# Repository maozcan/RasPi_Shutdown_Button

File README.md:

# Raspberry Pi Shutdown/Restart Button

## Hardware setup
Raspberry Pi GPIO pins are being used to send 'shutdown' command to turn off the Pi and to restart the device from off status.

Physical GPIO pin#7 turns off the system when you press switch#1 for 3+ seconds. The LED that is connected to pin#11 starts to blink and the shutdown routine is triggered. (LED is on when the system is operational.)

While the system is turned off, if the user presses the switch#2 which is connected to pin#5, RasPi gets a reboot signal and the system turns on.

EagleCad [schematic](/PiShutdownButton.sch) and [board](/PiShutdownButton.brd) layouts are available for download:

The board is then processed using CNC isolation routing; gcode created using php-gcode ULP and then the board is prepared on CNC machine. The pin headers have been soldered parallel to the board to help easier connection to RasPi board.

## Software setup

Python is used to handle the GPIO operations.

Install Python3 if it's not already installed. Also reinstall rpi.gpio package to ensure it is up to date.

```
> sudo apt-get install python3 rpi.gpio
```

Add the python script to the /root folder and paste in the following content.

```
> sudo touch /root/pi_shutdown.py
> sudo nano /root/pi_shutdown.py
```
The full code for the **pi_shutdown.py** script.
```python

#!/usr/bin/env python3
# Author: Mehmet Ozcan
# Harware setup ---->
# Microswitch_1 --> physical pins 1 and 7 on RPi (performs the shutdown)
# Microswitch_2 --> physical pins 5 and 9 on RPi (performs reset and also power on)
# LED and Resistor (220 ohm) --> LED+ pin connects to pin 11 on RPi
# .. LED- pin connects to the resistor and the resistor connects to pin 9 on RPİ (GND)
# Instructions ----->
# Install Python3: (and also reinstall rpi.gpio)
# > sudo apt-get install python3 rpi.gpio
# Add this file to /root folder
# > sudo touch /root/pi_shutdown.py
# > sudo nano /root/pi_shutdown.py (and paste all the content)
# > sudo chmod +x /root/pi_shutdown.py
# Add the script to (root user's) crontab so that it runs at each reboot
# > sudo crontab -e
# ... and add the following line to the bottom of the file
# @reboot sudo /usr/bin/python3 /root/pi_shutdown.py  > /root/pi_shutdown.log 2>&1

import os
import time
from time import sleep
import signal
import sys
from subprocess import call
import RPi.GPIO as GPIO

ledPin = 11
buttonPin = 7

def Shutdown(pin):
    pressedTime = time.monotonic()
    while GPIO.input(buttonPin):
        if time.monotonic()-pressedTime >= 3:
            blinkLed(3)
#            GPIO.output(ledPin, GPIO.LOW)
#            print("button pressed")
            call("halt", shell=False)
            break
#    os.system("sudo shutdown -h")
#    sleep(100)

def setup():
    GPIO.setmode(GPIO.BOARD)
    GPIO.setup(buttonPin, GPIO.IN, pull_up_down = GPIO.PUD_DOWN)
    GPIO.add_event_detect(buttonPin, GPIO.RISING, callback=Shutdown, bouncetime=200)
    GPIO.setup(ledPin, GPIO.OUT, initial=1)
    GPIO.setwarnings(False)
    return()

def blinkLed(intervals):
    for interval in range(intervals):
        GPIO.output(ledPin, GPIO.HIGH)
        time.sleep(1)
        GPIO.output(ledPin, GPIO.LOW)
        time.sleep(1)
        GPIO.output(ledPin, GPIO.HIGH)

try:
    setup()
    while True:
        time.sleep(1)

except KeyboardInterrupt: # trap a CTRL+C keyboard interrupt
    GPIO.cleanup() # resets all GPIO ports used by this program

```

Add the script to root user's crontab so that it will run at each reboot.

```
> sudo crontab -e
```
Add the following line to the bottom of the file
```
@reboot sudo /usr/bin/python3 /root/pi_shutdown.py  > /root/pi_shutdown.log 2>&1
```

Inspired from
https://www.element14.com/community/docs/DOC-78055/l/adding-a-shutdown-button-to-the-raspberry-pi-b

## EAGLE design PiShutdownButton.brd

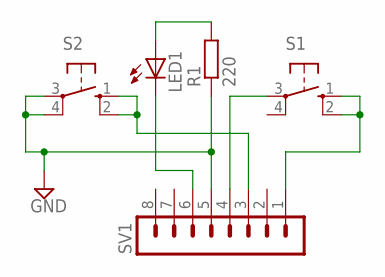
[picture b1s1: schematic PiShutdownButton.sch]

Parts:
LED1: LED3MM
R1: 220; 0204/5
S1, S2: 10-XX; B3F-10XX
SV1: MA08-1

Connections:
GND: R1.1, S2.3, S2.4 (P1), SV1.5
unnamed: S1.3, SV1.4
unnamed: S1.1 (S), S1.2 (S1), SV1.1
unnamed: S2.1 (S), S2.2 (S1), SV1.3
unnamed: LED1.A, R1.2
unnamed: LED1.K (C), SV1.6

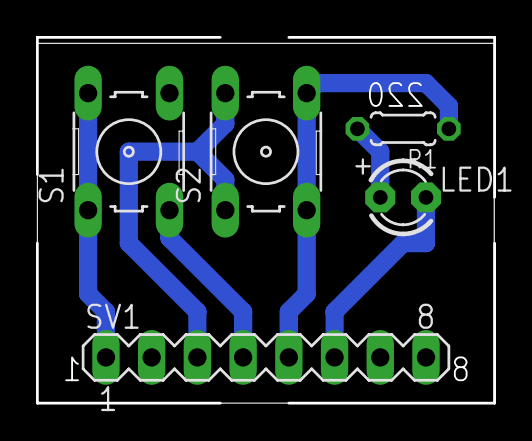
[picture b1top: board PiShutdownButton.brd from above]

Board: 2 copper layers, 25.4 x 20.3 mm, 5 parts (0 on the bottom side), 6 nets.

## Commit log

2017-06-09 Changed the layout of the instructions
